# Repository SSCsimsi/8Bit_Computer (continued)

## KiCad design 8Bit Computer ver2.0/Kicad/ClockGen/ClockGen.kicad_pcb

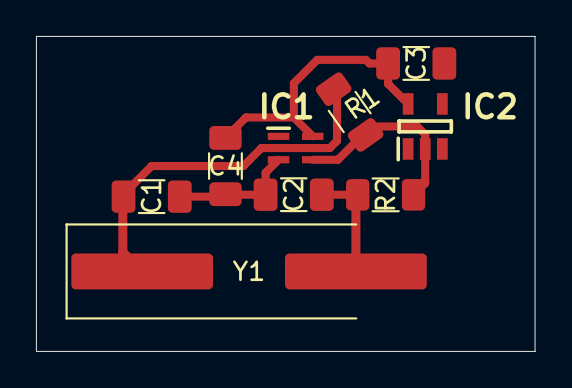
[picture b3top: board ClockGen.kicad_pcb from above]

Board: 2 copper layers, 27.7 x 17.5 mm, 9 parts (0 on the bottom side), 5 nets.

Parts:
C1, C2: 27pF; C_1206_3216Metric_Pad1.33x1.80mm_HandSolder
C3, C4: 100nF; C_1206_3216Metric_Pad1.33x1.80mm_HandSolder
IC1: SN74LVC1GU04DCKR; SOT65P210X110-5N
IC2: SN74LVC1G14DBVR; SOT95P280X145-5N
R1: 1M; R_1206_3216Metric_Pad1.30x1.75mm_HandSolder
R2: 330; R_1206_3216Metric_Pad1.30x1.75mm_HandSolder
Y1: 8MHz; Crystal_SMD_HC49-SD_HandSoldering

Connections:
+5V: C3.1, C4.1, IC1.5 (VCC), IC2.5 (VCC)
GND: C1.2, C2.2, C3.2, C4.2, IC1.3 (GND), IC2.3 (GND)
unnamed: C2.1, R2.2, Y1.2
unnamed: C1.1, IC1.2 (A), R1.1, Y1.1
unnamed: IC1.4 (Y), IC2.2 (A), R1.2, R2.1

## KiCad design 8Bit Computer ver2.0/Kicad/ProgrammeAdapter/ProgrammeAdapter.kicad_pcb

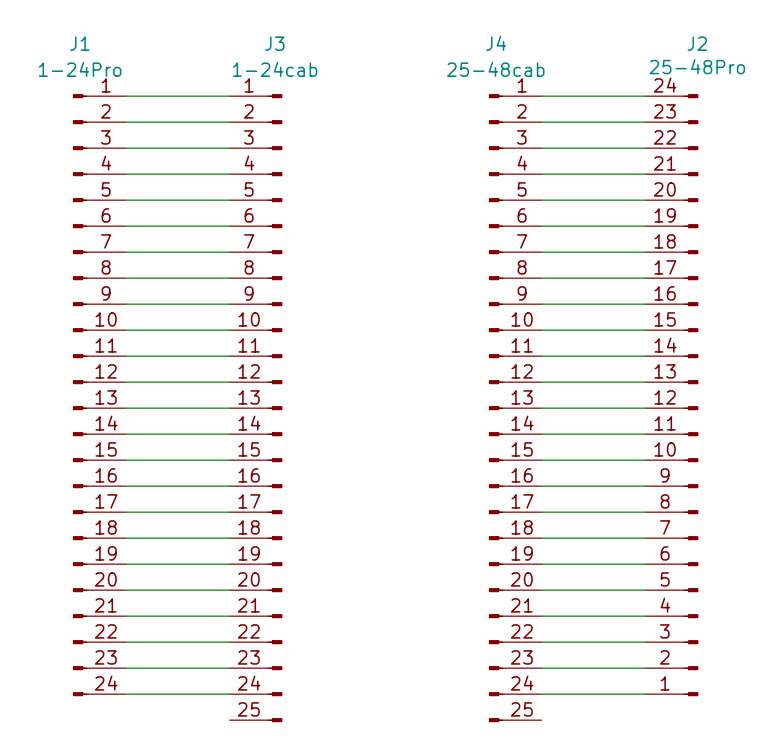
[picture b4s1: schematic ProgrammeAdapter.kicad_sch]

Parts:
J1: 1-24Pro; PinHeader_1x24_P2.54mm_Vertical
J2: 25-48Pro; PinHeader_1x24_P2.54mm_Vertical
J3: 1-24cab; PinHeader_1x25_P2.54mm_Vertical
J4: 25-48cab; PinHeader_1x25_P2.54mm_Vertical

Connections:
unnamed: J1.1, J3.1
unnamed: J1.2, J3.2
unnamed: J1.3, J3.3
unnamed: J1.4, J3.4
unnamed: J1.5, J3.5
unnamed: J1.6, J3.6
unnamed: J1.7, J3.7
unnamed: J1.8, J3.8
unnamed: J1.9, J3.9
unnamed: J1.10, J3.10
unnamed: J1.11, J3.11
unnamed: J1.12, J3.12
unnamed: J1.13, J3.13
unnamed: J1.14, J3.14
unnamed: J1.15, J3.15
unnamed: J1.16, J3.16
unnamed: J1.17, J3.17
unnamed: J1.18, J3.18
unnamed: J1.19, J3.19
unnamed: J1.20, J3.20
unnamed: J1.21, J3.21
unnamed: J1.22, J3.22
unnamed: J1.23, J3.23
unnamed: J1.24, J3.24
unnamed: J2.1, J4.24
unnamed: J2.2, J4.23
unnamed: J2.3, J4.22
unnamed: J2.4, J4.21
unnamed: J2.5, J4.20
unnamed: J2.6, J4.19
unnamed: J2.7, J4.18
unnamed: J2.8, J4.17
unnamed: J2.9, J4.16
unnamed: J2.10, J4.15
unnamed: J2.11, J4.14
unnamed: J2.12, J4.13
unnamed: J2.13, J4.12
unnamed: J2.14, J4.11
unnamed: J2.15, J4.10
unnamed: J2.16, J4.9
unnamed: J2.17, J4.8
unnamed: J2.18, J4.7
unnamed: J2.19, J4.6
unnamed: J2.20, J4.5
unnamed: J2.21, J4.4
unnamed: J2.22, J4.3
unnamed: J2.23, J4.2
unnamed: J2.24, J4.1

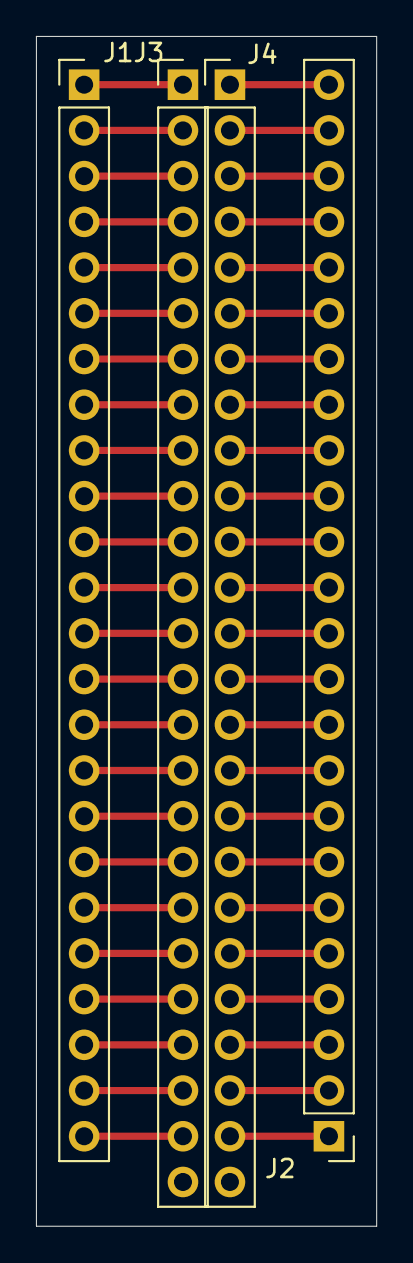
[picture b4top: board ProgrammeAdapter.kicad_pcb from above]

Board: 2 copper layers, 18.9 x 66.1 mm, 4 parts (0 on the bottom side), 48 nets.

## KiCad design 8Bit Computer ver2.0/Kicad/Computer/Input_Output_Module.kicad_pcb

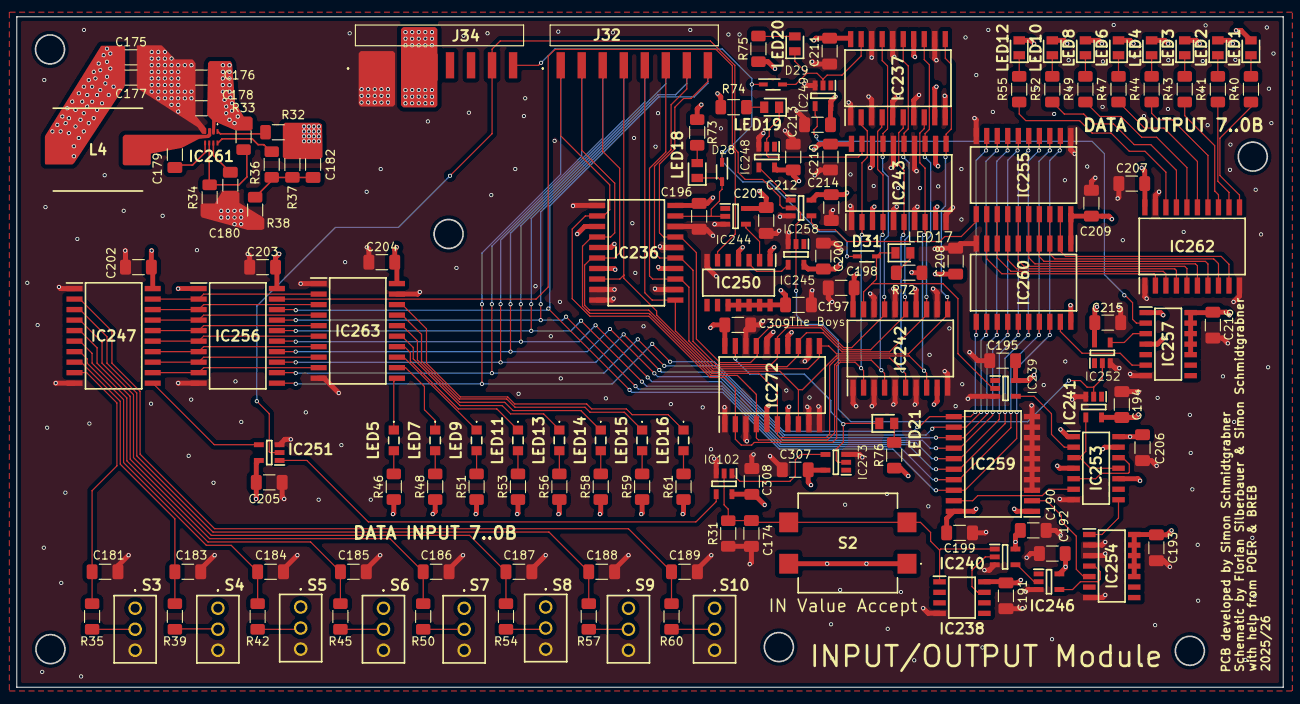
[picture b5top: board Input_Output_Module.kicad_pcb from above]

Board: 4 copper layers, 153.0 x 81.0 mm, 150 parts (1 on the bottom side), 123 nets.

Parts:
C174, C181, C183, C184, C185, C186, C187, C188, C189, C190, C191, C192, C193, C194, C195, C196, C197, C198, C199, C200, C201, C202, C203, C204, C205, C206, C207, C208, C209, C210, C211, C212, C213, C214, C215, C216, C307, C308, C309: 100nF; C_1206_3216Metric_Pad1.33x1.80mm_HandSolder
C175, C176, C177: 22uF; C_1206_3216Metric_Pad1.33x1.80mm_HandSolder
C178, C179: 0.1uF; C_1206_3216Metric_Pad1.33x1.80mm_HandSolder
C180: 22nF; C_1206_3216Metric_Pad1.33x1.80mm_HandSolder
C182: 300pF; C_1206_3216Metric_Pad1.33x1.80mm_HandSolder
D28, D29, D31: 1N4148WS-7-F; SOD2513X120N
IC102: SN74LVC1G32DBVR; SOT95P280X145-5N
IC236, IC237, IC242, IC243, IC272: SN74F521DWR; SOIC127P1030X265-20N
IC238: DS1100Z-150+; SOIC127P600X175-8N
IC239, IC241, IC244, IC245, IC246, IC248, IC249, IC252, IC273: SN74LVC1G14DBVR; SOT95P280X145-5N
IC240: SN74LVC1G86DBVR; SOT95P280X145-5N
IC247, IC255: SN74ABT574ADWR; SOIC127P1030X265-20N
IC250, IC253, IC254, IC257: SN74AHC74DR; SOIC127P600X175-14N
IC251, IC258: SN74LVC1G08DBVR; SOT95P280X145-5N
IC256, IC259, IC260: SN74ABT245BDWR; SOIC127P1030X265-20N
IC261: MP2338GTL-Z; MP2338GTLZ
IC262, IC263: SN74AHC540DWR; SOIC127P1030X265-20N
J32, J33, J34: M20-8890845; M208890845
L4: 6.8uH; INDPM108100X400N
LED1, LED2, LED3, LED4, LED6, LED8, LED10, LED12: LTST-C170KRKT; LEDC2012X120N
LED5, LED7, LED9, LED11, LED13, LED14, LED15, LED16: LTST-C171TBKT; LTSTC171TBKT
LED17, LED18, LED19, LED20, LED21: LTST-C170KFKT; LEDC2012X120N
R31, R35, R39, R42, R45, R50, R54, R57, R60: 4.7k; R_1206_3216Metric_Pad1.30x1.75mm_HandSolder
R32, R36, R38: 10k; R_1206_3216Metric_Pad1.30x1.75mm_HandSolder
R33: 191k; R_1206_3216Metric_Pad1.30x1.75mm_HandSolder
R34: 49.9k; R_1206_3216Metric_Pad1.30x1.75mm_HandSolder
R37: 90.9k; R_1206_3216Metric_Pad1.30x1.75mm_HandSolder
R40, R41, R43, R44, R47, R49, R52, R55: 390; R_1206_3216Metric_Pad1.30x1.75mm_HandSolder
R46, R48, R51, R53, R56, R58, R59, R61: 270; R_1206_3216Metric_Pad1.30x1.75mm_HandSolder
R72, R73, R74, R75, R76: 150; R_1206_3216Metric_Pad1.30x1.75mm_HandSolder
S2: B3FS-4055P; B3FS4055P
S3, S4, S5, S6, S7, S8, S9, S10: 2MS1T2B3M2QES

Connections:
/CMDIO0: IC236.2 (P0), IC237.2 (P0), IC242.2 (P0), IC243.2 (P0), IC272.2 (P0), J32.1
/CMDIO1: IC236.4 (P1), IC237.4 (P1), IC242.4 (P1), IC243.4 (P1), IC272.4 (P1), J32.2
/CMDIO2: IC236.6 (P2), IC237.6 (P2), IC242.6 (P2), IC243.6 (P2), IC272.6 (P2), J32.3
/CMDIO3: IC236.8 (P3), IC237.8 (P3), IC242.8 (P3), IC243.8 (P3), IC272.8 (P3), J32.4
/CMDIO4: IC236.11 (P4), IC237.11 (P4), IC242.11 (P4), IC243.11 (P4), IC272.11 (P4), J32.5
/CMDIO5: IC236.13 (P5), IC237.13 (P5), IC242.13 (P5), IC243.13 (P5), IC272.13 (P5), J32.6
/CMDIO6: IC236.15 (P6), IC237.15 (P6), IC242.15 (P6), IC243.15 (P6), IC272.15 (P6), J32.7
/CMDIO7: IC236.17 (P7), IC237.17 (P7), IC242.17 (P7), IC243.17 (P7), IC272.17 (P7), J32.8
/DATIO0: IC255.2 (1D), IC256.18 (B1), IC259.18 (B1), IC260.18 (B1), J33.1
/DATIO1: IC255.3 (2D), IC256.17 (B2), IC259.17 (B2), IC260.17 (B2), J33.2
/DATIO2: IC255.4 (3D), IC256.16 (B3), IC259.16 (B3), IC260.16 (B3), J33.3
/DATIO3: IC255.5 (4D), IC256.15 (B4), IC259.15 (B4), IC260.15 (B4), J33.4
/DATIO4: IC255.6 (5D), IC256.14 (B5), IC259.14 (B5), IC260.14 (B5), J33.5
/DATIO5: IC255.7 (6D), IC256.13 (B6), IC259.13 (B6), IC260.13 (B6), J33.6
/DATIO6: IC255.8 (7D), IC256.12 (B7), IC259.12 (B7), IC260.12 (B7), J33.7
/DATIO7: IC255.9 (8D), IC256.11 (B8), IC259.11 (B8), IC260.11 (B8), J33.8
/InputOutput/DAT_{dis}: D28.1 (K), D29.1 (K), D31.1 (K), J34.8
/InputOutput/GND: C174.2, C175.2, C176.1, C177.2, C178.1, C180.2, C181.1, C183.1, C184.1, C185.1, C186.1, C187.1, C188.1, C189.1, C190.1, C191.1, C192.1, C193.1, C194.1, C195.1, C196.1, C197.1, C198.1, C199.1, C200.1, C201.1, C202.1, C203.1, C204.1, C205.1, C206.1, C207.1, C208.1, C209.1, C210.1, C211.1, C212.1, C213.1, C214.1, C215.1, C216.1, C307.1, C308.1, C309.1, IC102.3 (GND), IC236.1 (~OE), IC236.9 (Q3), IC236.10 (GND), IC236.12 (Q4), IC236.16 (Q6), IC236.18 (Q7), IC237.1 (~OE), IC237.3 (Q0), IC237.5 (Q1), IC237.7 (Q2), IC237.10 (GND), IC237.12 (Q4), IC237.16 (Q6), IC237.18 (Q7), IC238.4 (GND), IC239.3 (GND), IC240.3 (GND), IC241.3 (GND), IC242.1 (~OE), IC242.3 (Q0), IC242.5 (Q1), IC242.7 (Q2), IC242.10 (GND), IC242.12 (Q4), IC242.16 (Q6), IC242.18 (Q7), IC243.1 (~OE), IC243.5 (Q1), IC243.7 (Q2), IC243.10 (GND), IC243.14 (Q5), IC243.16 (Q6), IC243.18 (Q7), IC244.3 (GND), IC245.3 (GND), IC246.3 (GND), IC247.1 (~OE), IC247.10 (GND), IC248.3 (GND), IC249.3 (GND), IC250.7 (GND), IC251.3 (GND), IC252.3 (GND), IC253.7 (GND), IC254.2 (1D), IC254.3 (1CLK), IC254.7 (GND), IC255.1 (~OE), IC255.10 (GND), IC256.10 (GND), IC257.7 (GND), IC258.3 (GND), IC259.3 (A2), IC259.4 (A3), IC259.5 (A4), IC259.6 (A5), IC259.7 (A6), IC259.8 (A7), IC259.9 (A8), IC259.10 (GND), IC260.10 (GND), IC261.4 (GND), IC262.1 (~OE1), IC262.10 (GND), IC262.19 (~OE2), IC263.1 (~OE1), IC263.10 (GND), IC263.19 (~OE2), IC272.1 (~OE), IC272.3 (Q0), IC272.9 (Q3), IC272.10 (GND), IC272.12 (Q4), IC272.16 (Q6), IC272.18 (Q7), IC273.3 (GND), J34.1, J34.2, R31.1, R34.2, R38.2, S3.3 (NC), S4.3 (NC), S5.3 (NC), S6.3 (NC), S7.3 (NC), S8.3 (NC), S9.3 (NC), S10.3 (NC)
/InputOutput/INBval0: C189.2, IC247.2 (1D), R60.1
/InputOutput/INBval1: C188.2, IC247.3 (2D), R57.1
/InputOutput/INBval2: C187.2, IC247.4 (3D), R54.1
/InputOutput/INBval3: C186.2, IC247.5 (4D), R50.1
/InputOutput/INBval4: C185.2, IC247.6 (5D), R45.1
/InputOutput/INBval5: C184.2, IC247.7 (6D), R42.1
/InputOutput/INBval6: C183.2, IC247.8 (7D), R39.1
/InputOutput/INBval7: C181.2, IC247.9 (8D), R35.1
/InputOutput/INval0: IC247.19 (1Q), IC256.2 (A1), IC263.2 (A1)
/InputOutput/INval1: IC247.18 (2Q), IC256.3 (A2), IC263.3 (A2)
/InputOutput/INval2: IC247.17 (3Q), IC256.4 (A3), IC263.4 (A3)
/InputOutput/INval3: IC247.16 (4Q), IC256.5 (A4), IC263.5 (A4)
/InputOutput/INval4: IC247.15 (5Q), IC256.6 (A5), IC263.6 (A5)
/InputOutput/INval5: IC247.14 (6Q), IC256.7 (A6), IC263.7 (A6)
/InputOutput/INval6: IC247.13 (7Q), IC256.8 (A7), IC263.8 (A7)
/InputOutput/INval7: IC247.12 (8Q), IC256.9 (A8), IC263.9 (A8)
/InputOutput/OUTval0: IC255.19 (1Q), IC260.2 (A1), IC262.9 (A8)
/InputOutput/OUTval1: IC255.18 (2Q), IC260.3 (A2), IC262.8 (A7)
/InputOutput/OUTval2: IC255.17 (3Q), IC260.4 (A3), IC262.7 (A6)
/InputOutput/OUTval3: IC255.16 (4Q), IC260.5 (A4), IC262.6 (A5)
/InputOutput/OUTval4: IC255.15 (5Q), IC260.6 (A5), IC262.5 (A4)
/InputOutput/OUTval5: IC255.14 (6Q), IC260.7 (A6), IC262.4 (A3)
/InputOutput/OUTval6: IC255.13 (7Q), IC260.8 (A7), IC262.3 (A2)
/InputOutput/OUTval7: IC255.12 (8Q), IC260.9 (A8), IC262.2 (A1)
/InputOutput/VBUS: C176.2, C178.2, IC261.2 (VIN), J34.3, J34.4, R33.2
/InputOutput/VCC: C175.1, C177.1, C182.1, C190.2, C191.2, C192.2, C193.2, C194.2, C195.2, C196.2, C197.2, C198.2, C199.2, C200.2, C201.2, C202.2, C203.2, C204.2, C205.2, C206.2, C207.2, C208.2, C209.2, C210.2, C211.2, C212.2, C213.2, C214.2, C215.2, C216.2, C307.2, C308.2, C309.2, IC102.5 (VCC), IC236.3 (Q0), IC236.5 (Q1), IC236.7 (Q2), IC236.14 (Q5), IC236.20 (VCC), IC237.9 (Q3), IC237.14 (Q5), IC237.20 (VCC), IC238.8 (VCC), IC239.5 (VCC), IC240.5 (VCC), IC241.5 (VCC), IC242.9 (Q3), IC242.14 (Q5), IC242.20 (VCC), IC243.3 (Q0), IC243.9 (Q3), IC243.12 (Q4), IC243.20 (VCC), IC244.5 (VCC), IC245.5 (VCC), IC246.5 (VCC), IC247.20 (VCC), IC248.5 (VCC), IC249.5 (VCC), IC250.1 (1~CLR), IC250.4 (1~PRE), IC250.10 (2~PRE), IC250.11 (2CLK), IC250.12 (2D), IC250.13 (2~CLR), IC250.14 (VCC), IC251.5 (VCC), IC252.5 (VCC), IC253.1 (1~CLR), IC253.4 (1~PRE), IC253.10 (2~PRE), IC253.13 (2~CLR), IC253.14 (VCC), IC254.10 (2~PRE), IC254.11 (2CLK), IC254.12 (2D), IC254.13 (2~CLR), IC254.14 (VCC), IC255.20 (VCC), IC256.1 (DIR), IC256.20 (VCC), IC257.1 (1~CLR), IC257.4 (1~PRE), IC257.10 (2~PRE), IC257.11 (2CLK), IC257.12 (2D), IC257.13 (2~CLR), IC257.14 (VCC), IC258.5 (VCC), IC259.1 (DIR), IC259.20 (VCC), IC260.1 (DIR), IC260.20 (VCC), IC262.20 (VCC), IC263.20 (VCC), IC272.5 (Q1), IC272.7 (Q2), IC272.14 (Q5), IC272.20 (VCC), IC273.5 (VCC), L4.1, LED1.2 (A), LED2.2 (A), LED3.2 (A), LED4.2 (A), LED6.2 (A), LED8.2 (A), LED10.2 (A), LED12.2 (A), R32.1, R37.2, R46.1, R48.1, R51.1, R53.1, R56.1, R58.1, R59.1, R61.1, R72.1, R73.1, R74.1, R75.1, R76.1, S2.1 (COM_1), S2.2 (COM_2), S3.1 (NO), S4.1 (NO), S5.1 (NO), S6.1 (NO), S7.1 (NO), S8.1 (NO), S9.1 (NO), S10.1 (NO)
/InputOutput/~CLKd: IC241.2 (A), IC245.2 (A), IC251.2 (B), IC252.2 (A), IC258.2 (B), J34.7
unnamed: C182.2, R36.2, R37.1, R38.1
unnamed: D28.2 (A), IC236.19 (~P_=_Q), IC244.2 (A), LED18.1 (K)
unnamed: D29.2 (A), IC237.19 (~P_=_Q), IC249.2 (A), LED20.1 (K)
unnamed: D31.2 (A), IC239.2 (A), IC242.19 (~P_=_Q), LED17.1 (K)
unnamed: IC102.1 (A), IC273.4 (Y)
unnamed: C174.1, IC102.2 (B), IC238.1 (IN), IC240.1 (A), R31.2, S2.3 (NO_1), S2.4 (NO_2)
unnamed: IC102.4 (Y), IC251.1 (A)
unnamed: IC238.7 (TAP_1), IC240.2 (B)
unnamed: IC239.4 (Y), IC253.2 (1D)
unnamed: IC240.4 (Y), IC246.2 (A)
unnamed: IC241.4 (Y), IC253.3 (1CLK), IC253.11 (2CLK)
unnamed: IC243.19 (~P_=_Q), IC248.2 (A), LED19.1 (K)
unnamed: IC244.4 (Y), IC250.2 (1D)
unnamed: IC245.4 (Y), IC250.3 (1CLK)
unnamed: IC246.4 (Y), IC254.4 (1~PRE)
unnamed: IC247.11 (CLK), IC251.4 (Y)
unnamed: IC248.4 (Y), IC258.1 (A)
unnamed: IC249.4 (Y), IC257.2 (1D)
unnamed: IC250.6 (1~Q), IC256.19 (~OE)
unnamed: IC252.4 (Y), IC257.3 (1CLK)
unnamed: IC253.5 (1Q), IC253.12 (2D)
unnamed: IC253.6 (1~Q), IC259.19 (~OE)
unnamed: IC253.8 (2~Q), IC254.1 (1~CLR)
unnamed: IC254.5 (1Q), IC259.2 (A1)
unnamed: IC255.11 (CLK), IC258.4 (Y)
unnamed: IC257.6 (1~Q), IC260.19 (~OE)
unnamed: C179.2, IC261.5 (BST)
unnamed: IC261.6 (EN), R33.1, R34.1
unnamed: IC261.8 (FB), R36.1
unnamed: IC261.1 (PG), R32.2
unnamed: C180.1, IC261.7 (SS)
unnamed: C179.1, IC261.3 (SW), L4.2
unnamed: IC262.18 (Y1), R55.2
unnamed: IC262.17 (Y2), R52.2
unnamed: IC262.16 (Y3), R49.2
unnamed: IC262.15 (Y4), R47.2
unnamed: IC262.14 (Y5), R44.2
unnamed: IC262.13 (Y6), R43.2
unnamed: IC262.12 (Y7), R41.2
unnamed: IC262.11 (Y8), R40.2
unnamed: IC263.18 (Y1), LED16.1 (K)
unnamed: IC263.17 (Y2), LED15.1 (K)
unnamed: IC263.16 (Y3), LED14.1 (K)
unnamed: IC263.15 (Y4), LED13.1 (K)
unnamed: IC263.14 (Y5), LED11.1 (K)
unnamed: IC263.13 (Y6), LED9.1 (K)
unnamed: IC263.12 (Y7), LED7.1 (K)
unnamed: IC263.11 (Y8), LED5.1 (K)
unnamed: IC272.19 (~P_=_Q), IC273.2 (A), LED21.1 (K)
unnamed: LED1.1 (K), R40.1
unnamed: LED2.1 (K), R41.1
unnamed: LED3.1 (K), R43.1
unnamed: LED4.1 (K), R44.1
unnamed: LED5.2 (A), R46.2
unnamed: LED6.1 (K), R47.1
unnamed: LED7.2 (A), R48.2
unnamed: LED8.1 (K), R49.1
unnamed: LED9.2 (A), R51.2
unnamed: LED10.1 (K), R52.1
unnamed: LED11.2 (A), R53.2
unnamed: LED12.1 (K), R55.1
unnamed: LED13.2 (A), R56.2
unnamed: LED14.2 (A), R58.2
unnamed: LED15.2 (A), R59.2
unnamed: LED16.2 (A), R61.2
unnamed: LED17.2 (A), R72.2
unnamed: LED18.2 (A), R73.2
unnamed: LED19.2 (A), R74.2
unnamed: LED20.2 (A), R75.2
unnamed: LED21.2 (A), R76.2
unnamed: R35.2, S3.2 (COM)
unnamed: R39.2, S4.2 (COM)
unnamed: R42.2, S5.2 (COM)
unnamed: R45.2, S6.2 (COM)
unnamed: R50.2, S7.2 (COM)
unnamed: R54.2, S8.2 (COM)
unnamed: R57.2, S9.2 (COM)
unnamed: R60.2, S10.2 (COM)

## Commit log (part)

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2024-05-29 stuff
2024-05-31 awsf
2024-06-06 partsadd
2025-04-18 asdasdasd
2025-04-18 added buffer to the list + made 8bit parallel adder
2025-04-29 reorganized some stuff
2025-05-22 translation from 74 series designs to logical designs
2025-06-12 created the adder file
    it's empty as of now
2025-06-21 added commands to the list + redid previous order
2025-06-27 worked on adder/subtractor
    subtraction command vanishes after the initial input, need some way to save the commands for one clockcycle
2025-06-27 finished adder/subtractor
    fixed the aforementioned problem with a d-latch
2025-06-27 Rewrote Explanations
2025-06-30 aasdad
2025-07-27 Update Comparator.dig
    should be done
2025-07-27 Changed timing for a few files
2025-08-06 Started work on the ALU
    + a few fixes for Adder/Subtractor and Comparator
    + ADC (Add With Carry) command for Adder/Subtractor
    - removed Command Decoder as it was redundant
2025-08-06 Finished the Incrementor
    + added Incrementor to ALU
    ~ updated commands
2025-08-07 Add Shift Register to ALU
    + added control logic to shift reg
2025-08-15 Update Flag Register.dig
    + fixed the timing
    ~ not sure about D-flip-flops with drivers, could use buffers instead
2025-08-15 Added Flags Register to the ALU
    - still need to hook up the LDC and LDF lines of the flags register to the adder
    - need to add the outputs for LDC and LDF to the adder
2025-08-20 Update ALU.dig
    + added A/B/C registers
2025-08-20 Update commands.xlsx
    added and changed previously discussed commands
2025-08-21 Finished ALU for now
    + created CPU.dig
2025-09-02 added program counter
    - the clear input still needs to be connected
    - a 16 bit register is still needed for RAM addresses
    - maybe timers + interrupts
2025-09-06 +text in ALU.dig
    idea for saving 8 input or gates
2025-09-08 parts
    added some better chip versions
    added some datasheets
    added some Websites
2025-09-29 parts
    added flash
    added sram
    added some prices
    added 8in or diagram
2025-10-01 Update commands.xlsx
    set previous shift commands to deprecated
2025-10-02 partslist
    added Register
    added new MUX
2025-10-02 combined the 8 different 8 input or gates into 2
2025-10-02 Partslist
    added BUY links to mouser
    specified Flash 512k*16
2025-10-02 Buffer
2025-10-03 parts,Kicad
    added Parts into Kicad
    |Waiting for CAD Model of SN74HCS574DGSR|
    started Kicad Schematic:
    added ALU->BinaryXOR/AND/OR/NOT
2025-10-04 KicadParts
    added the Parts as .zip
2025-10-06 parts
    added new NOR flash M29F800FT
2025-10-07 Changes:
    - readded barrel shifter
    - made changes to shift register to save xor gates
2025-10-07 added RAM
    still needs to be verified
2025-10-09 named commands
    + each command now has a hex value
    * renamed the ram inputs to make more sense
    + added simple explanations to the ram commands in the excel file
2025-10-09 changed comparison values to hex format
2025-10-10 Update Incrementor.dig
    - design of incrementor is now closer to the planned real design
    - may actually need to add a warning to future programming guides !!!
2025-10-10 parts,Kicad
    parts:
    changed 8xDlatch HCS to ABT 574
    waiting for SRAM CAD Model
    Kicad:
    imported AHC types of ICs
    added ProgrammeCounter
2025-10-10 parts, Kicad
    parts:
    added MUX 157 for BarrelShiftReg
    Kicad:
    began with BarrelShiftRegister
2025-10-11 small fixes
2025-10-11 partsList, Kicad
    parts:
    added faster Comparator 521
    added 1CH XOR
    added 8Bit and 16Bit Driver 245, 16245
    ->they need pullUp resistors for High-Z when power on
    Kicad:
2025-10-12 Kicad
    added Register 2(0x22 u 0x23) and 3(0x13 u 0x14)
    added BarrelShiftRegister
    added AdderSubstractor
    added cmd Comparators to the bitwise and binary Logic
2025-10-12 adjusted command values
2025-10-13 finished lookup table, still needs testing
    not sure on the actual operation
2025-10-14 changed the flash control logic
    changed from a lookup table to a single bit bus, since the previous solution would use up nearly double the amount of comparators
2025-10-14 Kicad
    changed the comp values to the new ones
2025-10-15 Programmer Xgecu T76
    added Programmer Programme for T76
2025-10-17 Kicad
    added Programmer Adapter
2025-10-19 added data to address bus interface
2025-10-20 changed LN line to a direct connection, as it is not a bus
2025-10-23 parts
    added 8channel not
    added possible Leds
    added possible switches
2025-10-24 added input control
2025-10-24 changed timing again
    it is a bit slow to reenable the flash now
2025-10-24 changed the input leds so that they show the value stored in the input register
2025-10-24 Kicad,parts
    Kicad:
    worked on Flash memory
    began RAM
    parts:
    added Delay Chip for Flash
2025-10-27 Kicad, parts
    Parts:
    added Leds
    Kicad:
    added Input Output
    changed Q bus to DAT bus
2025-10-28 Kicad, parts
    parts:
    added Flipswitch
    added Inductor for PSU
    added Step-Down Conv chip MP2338GTL
    Kicad:
    added Step-Down Conv circuit for 20V VBUS to 5V VCC
2025-11-01 Kicad
    changed to module version
2025-11-06 Kicad, folders
    Kicad:
    added Computer Schematic pdf of the module version
    added Clock Gen pdf Schemtics and PCB
    folders:
    changed old Computer versions to OLD_
2025-11-09 coded a short test programme
    an error comes up during the 5th operation, which is an STB operation, for which a value is loaded from rom
2025-11-09 found 2 short circuits within the alu
2025-11-09 still debugging (this time in the alu)
    found that the registers needed a small delay
2025-11-09 ...the hex display was the wrong way around
2025-11-09 Update Flag Register.dig
    the carry out output of the flag reg was connected to the overflow flip flop
2025-11-13 Create test.txt
    the next few operations need to make use of the current value in A in order to ensure a proper test of all the commands used
2025-11-16 test programme
    continued adding commands to be tested + translated to hex
2025-11-20 testing, found something
    the format of 16 bit storage in digital is Little endian, even though the programme says otherwise
2025-11-20 found the error
    the value on the data bus was disappearing before the command could execute. the fix was to add a data flip flop to hold the value for an additional clock tick
2025-11-20 Update test.txt
    added a warning, as the flag register currently is a random numbers generator
2025-11-20 marked all the tested commands
2025-11-27 Kicad, parts
    parts:
    added Mux 4:1 for CLK
    added LM555
    Kicad:
    added some Diodes for Flash disable
    fixed wrong routing of flag register
2025-12-05 worked on the test code
2025-12-07 Kicad
    added the Programme Counter und Dat to adr module
2025-12-08 worked on the test programme
    still needs to be translated to hex, also still missing the input commands
2025-12-08 error found
    translated the code to hex, the simulation experiences a short at line 42
2025-12-08 found the error...
    i forgot a diode to the address disable bus
2025-12-08 testing
    the bit pattern i designed does not show up, it is 0D0D instead of 5555
2025-12-08 changes
    + added 8 by 8 pixel display
    * found the delay within the registers to be useless
2025-12-09 changes to commands
    + added the store inputs command
    - had to change the values for the load inputs, load unread, store outputs and load outputs commands
    + added two commands to the screen
2026-01-06 Kicad
    added 10pin 2,54mm Header
    finished ALU PCB and added pin Header for extra use (DAT,ADR,CMD,Ddis,CLK)
    31.12-06.01 about +60hr for ALU
2026-01-08 started writing the assembler
2026-01-08 Kicad
    added Schematic PDF V2.0
    added PCB PDF V2.0
    renamed the old PDFs
2026-01-09 Update mistakes layout.txt
    ~ 5 hours
2026-01-10 Update mistakes layout.txt
    problematic mistakes are marked with an exclamation mark, problems that should not impact the functionality of the computer are without the exclamation mark
2026-01-10 Kicad, PCB Fix
    fixed the errors on the PCB
    added mounting holes
    added GND panels on Top and Bot Layer
    added 100uF
2026-01-15 sorted some things. added bom
2026-01-22 continued work
    commit seems wierd
2026-01-29 finished the assembler
    had some "assistance"
2026-01-31 forgot to add to last commit
2026-02-11 updated T76 software, Kicad bugs
    changed the inverting outs of IC199 to non inverting
    changed Pin of CMD decoder IC237 0x2A from GND to VCC (pin5)
    deleted diode d30
    changed silkscreen of the Clock gen mux from 0 1 555 to 1 0 555 and buttonclk from 1 0 to 0 1
    changed the DS1100-150+ of the edge detector to an or gate SN74HCS32
2026-02-12 strings show error
    Failed to execute MI command:
    -var-create - * &((()._M_local_buf))
2026-02-12 kicad incrementor cmd comp fix
    fixed wrong hex to bin to pins
2026-02-13 changed the flash in the simulation
    it can now be programmed the same way that the real computer will have to be programmed in order to be able to test easily,
    the rewritten code with the new command names does not yet work tho
2026-02-15 added logic gate symbols
2026-02-24 fixed
2026-02-26 fixed compiler
    text mode inserts new line characters
    > changed the files' mode to binary
2026-02-27 added visualization for the busses in the simulation
2026-02-28 documentation files, CPU layout changes
2026-03-01 overview images added
2026-03-05 Kicad
    fixed some design errors(dat dis DistShiftreg, wrong cmd pins)
    added description to every CMD for better debug, use CTRL+f and use option "Whole words only" to search e.g. inc
2026-03-06 changed addresses for jumps
2026-03-06 fixes
    fixed timing for dat to adr register
    added a new short test programme for dat to adr register
2026-03-06 add images
2026-03-10 moved code + new image
2026-03-14 added functionality to the assembler
    when writing code, lines need to be started with semicolons
    when assembling the binary files, the assembler will rewrite the line numbers in the code file, helping with writing jump commands
    - addresses next to jump commands will however not be changed > still needs to be fixed
2026-03-15 Fixed some Design bugs
    added some pdfs
2026-03-15 empty lines in assembler + programme more readable
2026-03-15 added labels
    untested for now; should add the ability to reuse labels at different positions, by changing the position variable to a list
2026-03-16 debugging lines in main + add label to code
2026-03-16 fixed labels in assembler
2026-03-16 added labels and adr to dat to code.txt
2026-03-17 part 1 of changing to A4
2026-03-18 fixed code + fixed error output in main.cpp
    the address bus disabling did not work previously, so it had to be moved by one cycle
2026-03-19 changed page numbers, compressed ROOT file from A1 to A4
2026-03-25 add documentation
2026-03-31 worked on calculator
    it still needs error detection along with multiplication and division
    multiplication and division could be realized with the shift register, where the divisor/multiplier is separated into all their bits, and then if one bit is high, the first value gets shifted by a sp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
2026-04-02 small fixes for the assembler
    assembler now allows labels containing the names of other labels
2026-04-03 fixes
    tried to make the input programme wait until the button is let go of and then allow another value to be stored.
2026-04-22 added stuff
2026-04-27 moved some stuff
    - reverted the barrel shifter to the previous incorrect design
    - wrote a short test prgramme
2026-04-27 stuff
    loading from ram still does not work
